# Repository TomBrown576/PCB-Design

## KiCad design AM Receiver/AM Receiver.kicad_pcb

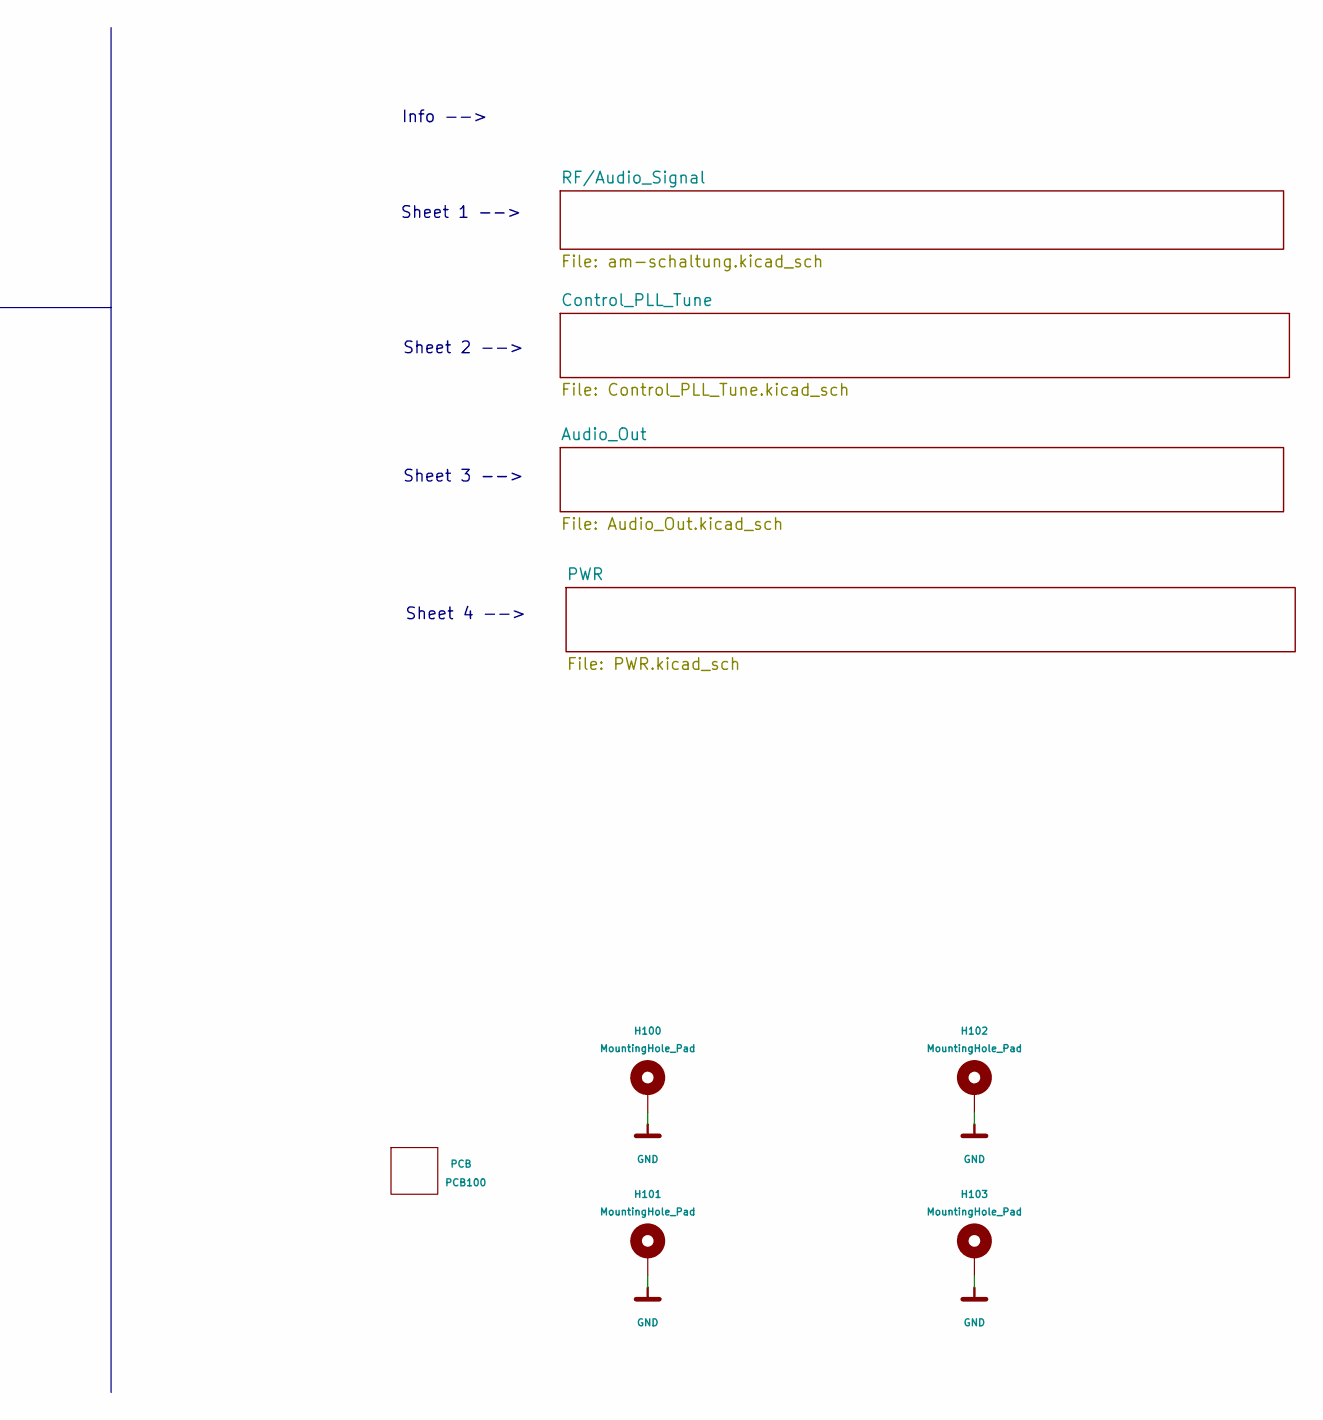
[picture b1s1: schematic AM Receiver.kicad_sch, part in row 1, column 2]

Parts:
H100, H101, H102, H103: MountingHole_Pad; MountingHole_3.2mm_M3_Pad
PCB100: PCB

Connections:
GND: H100.1 (1_1), H101.1 (1_1), H102.1 (1_1), H103.1 (1_1); also elsewhere on the board

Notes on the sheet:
Date 01.07.2026
Sheet 1 -->
Projekt Am Receiver with quadratur mixer
Info -->
Sheet 4 -->
Rev. 1.0
Sheet 3 -->
Name T.Brown
Sheet 2 -->
Changes, Modifications V1.0 Initial Revision Input Voltage 12V ... 15V
Gruppe Gruppe 12
Revision History

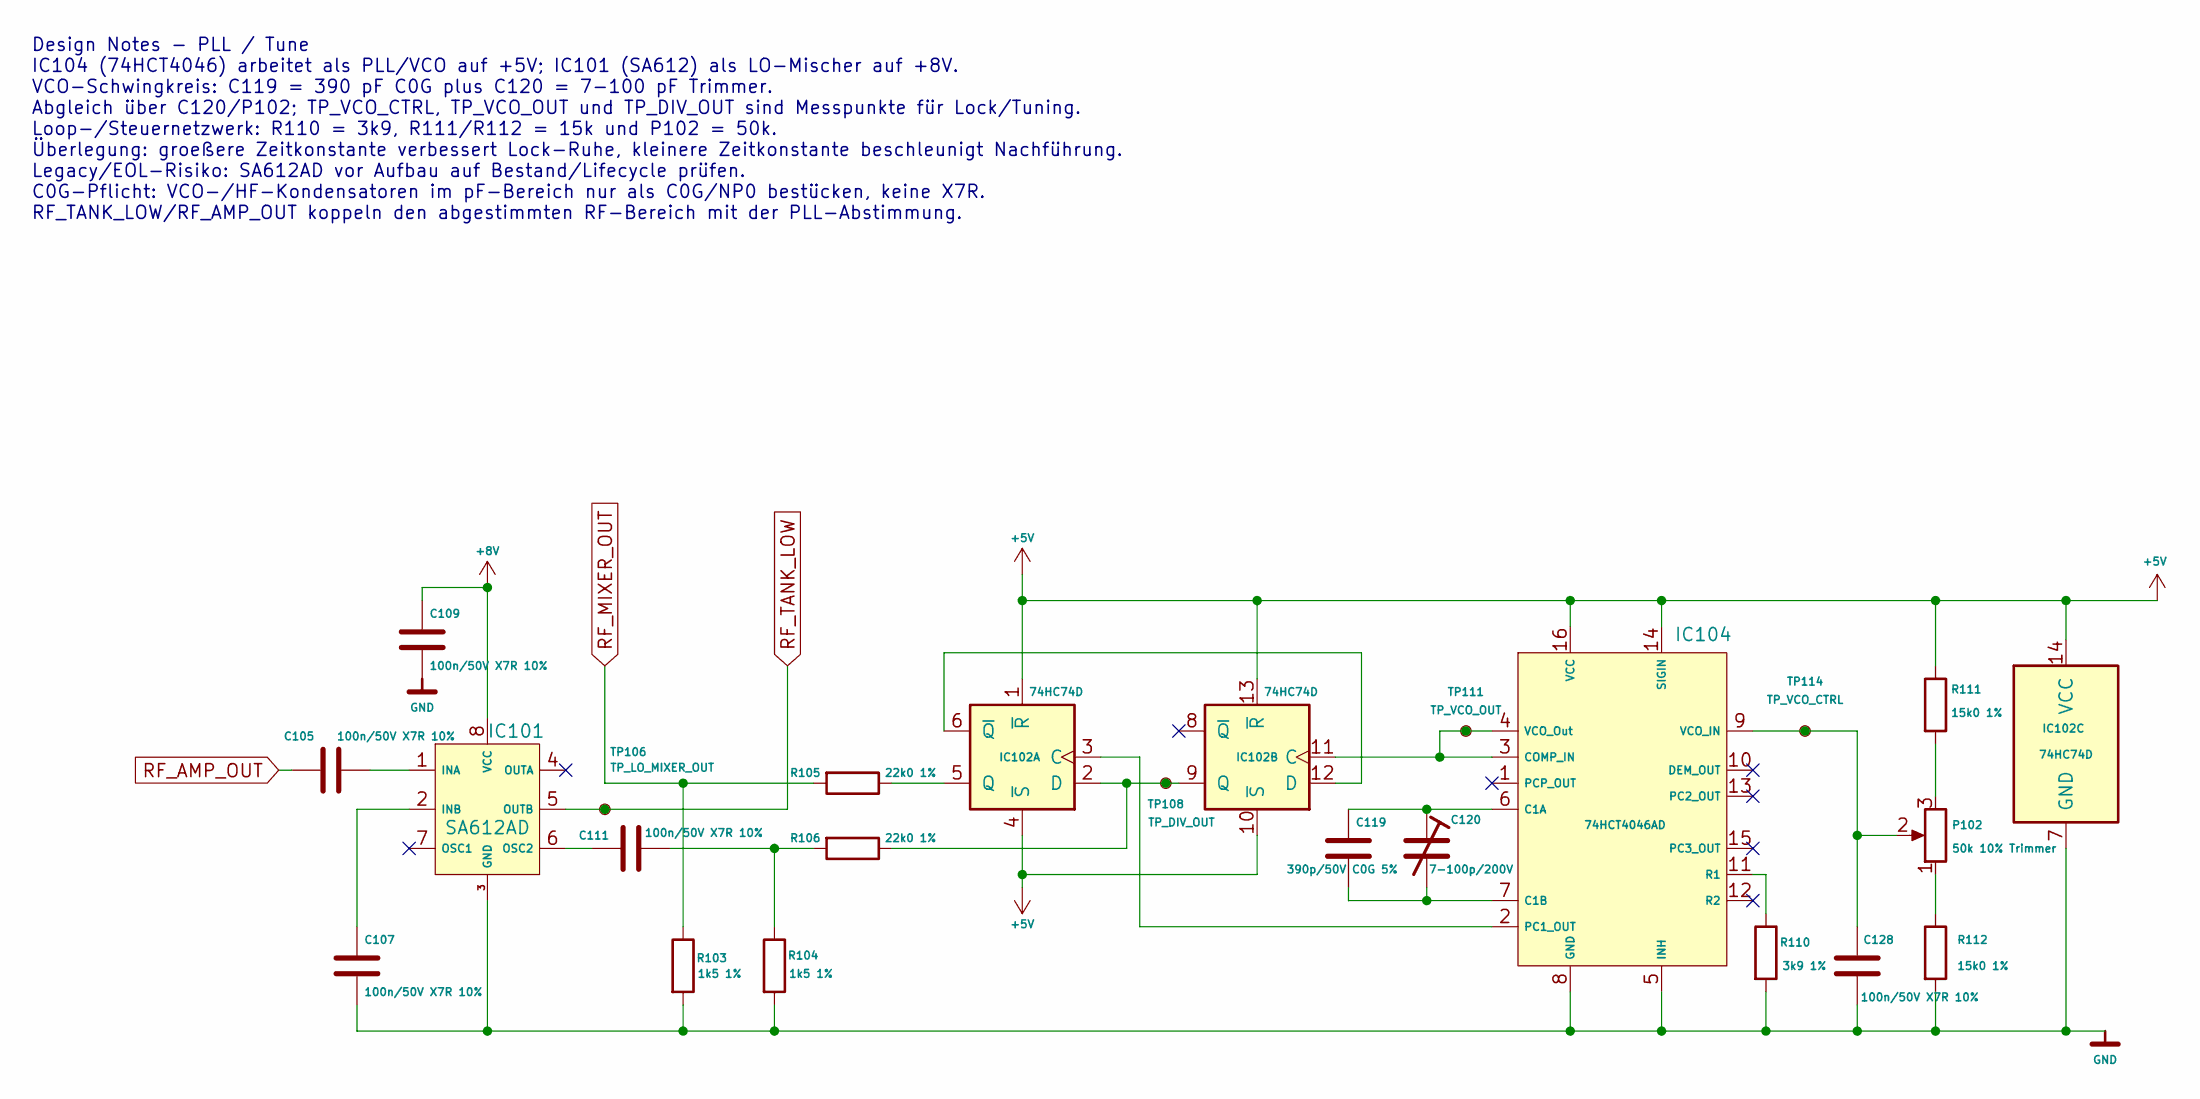
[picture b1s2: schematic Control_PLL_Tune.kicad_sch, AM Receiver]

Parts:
C105, C107, C109, C111, C128: 100n/50V X7R 10%; C_0603_1608Metric_Pad1.08x0.95mm_HandSolder
C119: 390p/50V C0G 5%; C_0603_1608Metric_Pad1.08x0.95mm_HandSolder
C120: 7-100p/200V; Vishay_BFC280907015_Trimmer_7-100pF
IC101: SA612AD; SOIC-8_3.9x4.9mm_P1.27mm
IC102: 74HC74D; SOIC-14_3.9x8.7mm_P1.27mm
IC104: 74HCT4046AD; SOIC-16_3.9x9.9mm_P1.27mm
P102: 50k 10% Trimmer; Potentiometer_Bourns_3386P_Vertical
R103, R104: 1k5 1%; R_0603_1608Metric_Pad0.98x0.95mm_HandSolder
R105, R106: 22k0 1%; R_0603_1608Metric_Pad0.98x0.95mm_HandSolder
R110: 3k9 1%; R_0603_1608Metric_Pad0.98x0.95mm_HandSolder
R111, R112: 15k0 1%; R_0603_1608Metric_Pad0.98x0.95mm_HandSolder
TP106: TP_LO_MIXER_OUT; TestPoint_Pad_D1.0mm
TP108: TP_DIV_OUT; TestPoint_Pad_D1.0mm
TP111: TP_VCO_OUT; TestPoint_Pad_D1.0mm
TP114: TP_VCO_CTRL; TestPoint_Pad_D1.0mm

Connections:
+5V: IC102.1 (~R), IC102.4 (~S), IC102.10 (~S), IC102.13 (~R), IC102.14 (VCC), IC104.14 (SIGIN), IC104.16 (VCC), R111.1; also elsewhere on the board
+8V: C109.1, IC101.8 (VCC); also elsewhere on the board
GND: C107.2, C109.2, C128.2, IC101.3 (GND), IC102.7 (GND), IC104.5 (INH), IC104.8 (GND), R103.2, R104.2, R110.2, R112.2; also elsewhere on the board
unnamed: C111.1, R104.1, R106.2
unnamed: C105.1, IC101.1 (INA)
unnamed: C107.1, IC101.2 (INB)
unnamed: C111.2, IC101.6 (OSC2)
unnamed: IC102.3 (C), IC104.2 (PC1_OUT)
unnamed: IC102.2 (D), IC102.9 (Q), R106.1, TP108.1 (1_1)
unnamed: IC102.5 (Q), R105.1
unnamed: IC102.6 (~Q), IC102.12 (D)
unnamed: IC102.11 (C), IC104.3 (COMP_IN), IC104.4 (VCO_Out), TP111.1 (1_1)
unnamed: C119.1, C120.1, IC104.6 (C1A)
unnamed: C119.2, C120.2, IC104.7 (C1B)
unnamed: IC104.11 (R1), R110.1
unnamed: C128.1, IC104.9 (VCO_IN), P102.2, TP114.1 (1_1)
unnamed: P102.1, R112.1
unnamed: P102.3, R111.2
RF_AMP_OUT: C105.2; also elsewhere on the board
RF_MIXER_OUT: R103.1, R105.2; also elsewhere on the board
RF_TANK_LOW: IC101.5 (OUTB), TP106.1 (1_1); also elsewhere on the board

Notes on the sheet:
Design Notes - PLL / Tune IC104 (74HCT4046) arbeitet als PLL/VCO auf +5V; IC101 (SA612) als LO-Mischer auf +8V. VCO-Schwingkreis: C119 = 390 pF C0G plus C120 = 7-100 pF Trimmer. Abgleich über C120/P102; TP_VCO_CTRL, TP_VCO_OUT und TP_DIV_OUT sind Messpunkte für Lock/Tuning. Loop-/Steuernetzwerk: R1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

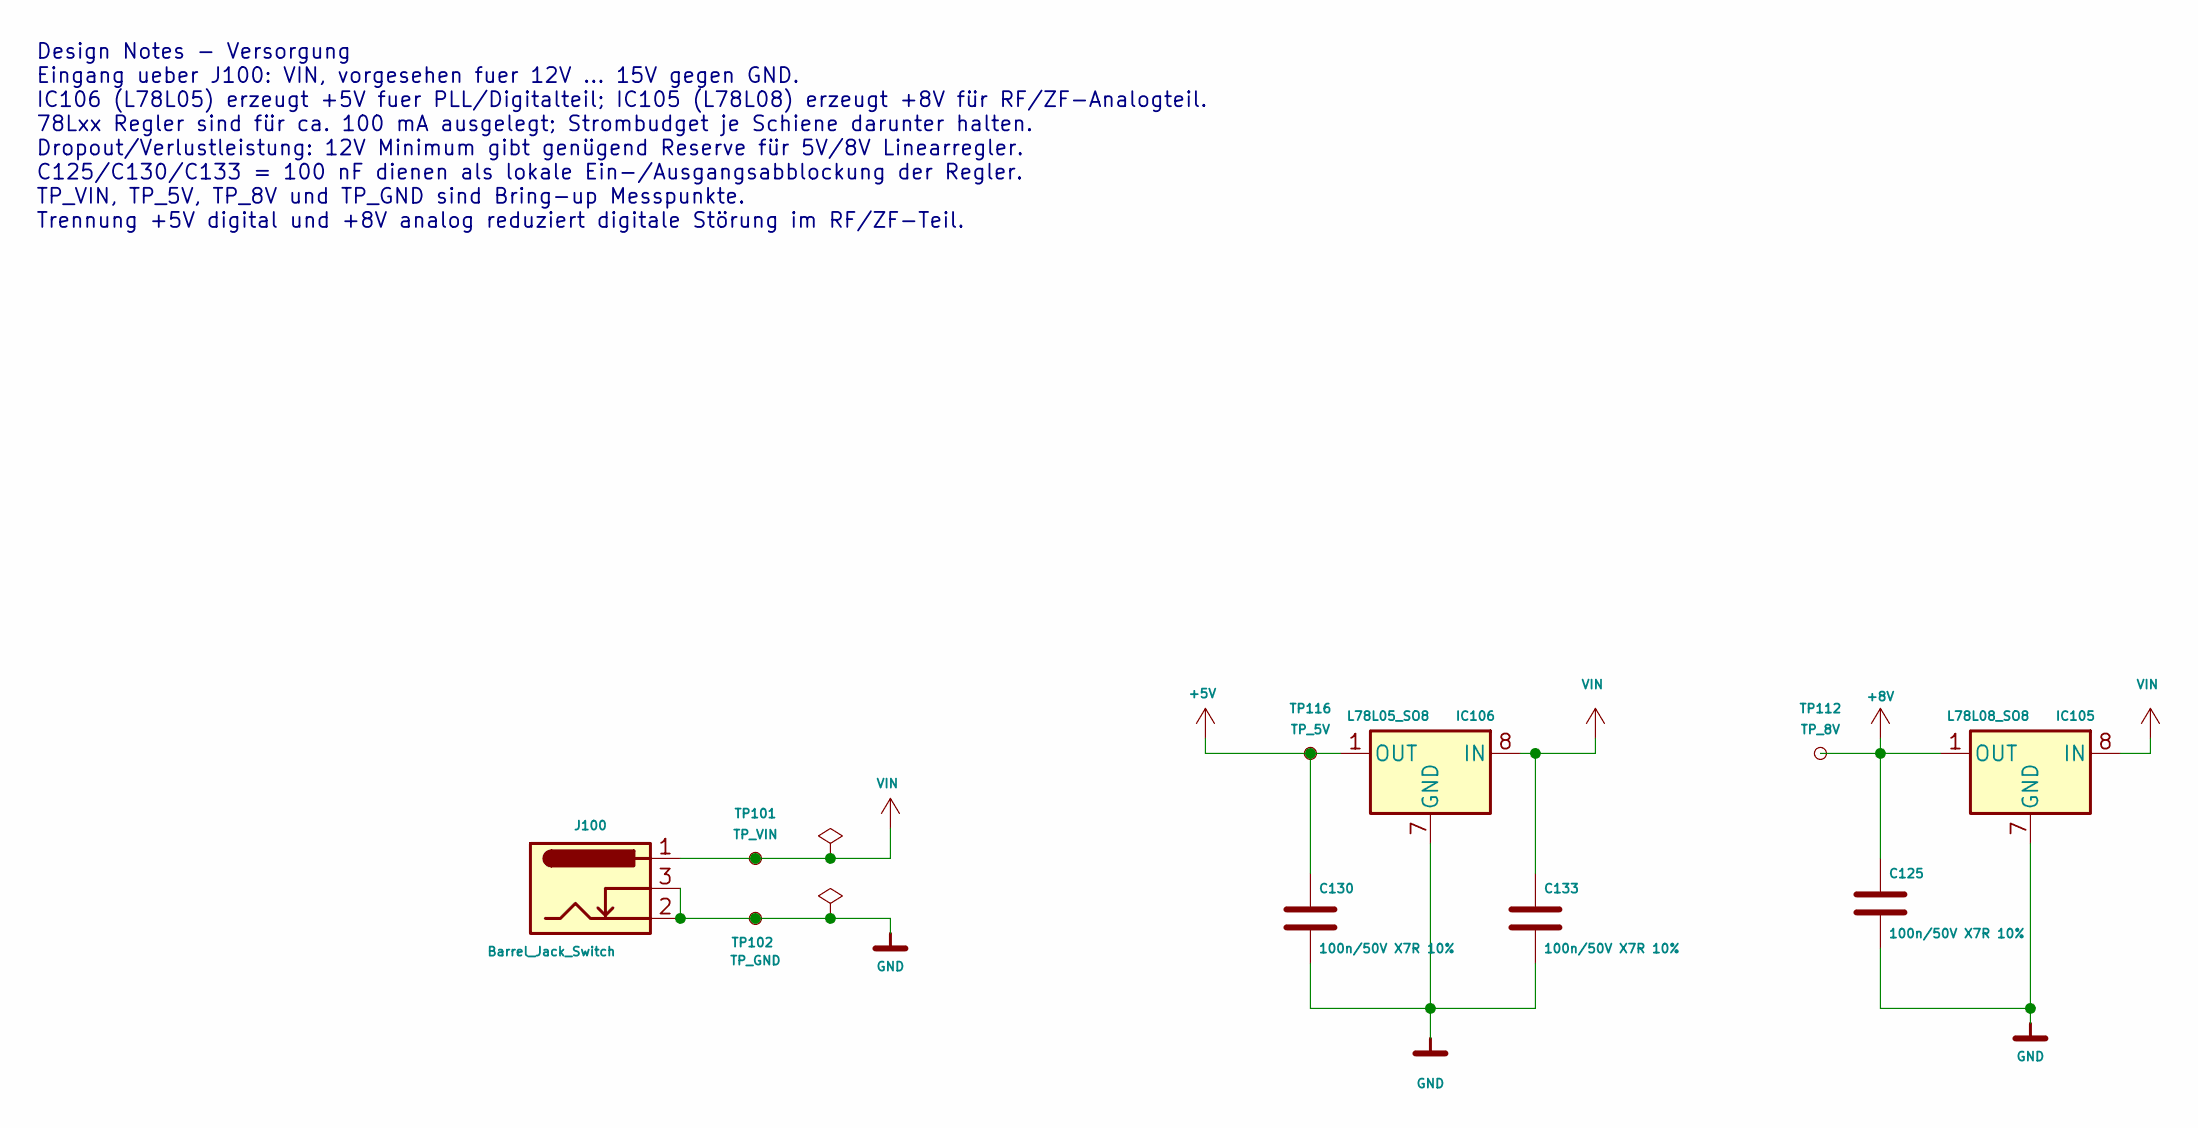
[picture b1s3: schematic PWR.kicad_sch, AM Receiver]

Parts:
C125, C130, C133: 100n/50V X7R 10%; C_0603_1608Metric_Pad1.08x0.95mm_HandSolder
IC105: L78L08_SO8; SOIC-8_3.9x4.9mm_P1.27mm
IC106: L78L05_SO8; SOIC-8_3.9x4.9mm_P1.27mm
J100: Barrel_Jack_Switch; BarrelJack_CUI_PJ-102AH_Horizontal
TP101: TP_VIN; TestPoint_Pad_D1.0mm
TP102: TP_GND; TestPoint_Pad_D1.0mm
TP112: TP_8V; TestPoint_Pad_D1.0mm
TP116: TP_5V; TestPoint_Pad_D1.0mm

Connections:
+5V: C130.1, IC106.1 (OUT), TP116.1 (1_1); also elsewhere on the board
+8V: C125.1, IC105.1 (OUT), TP112.1 (1_1); also elsewhere on the board
GND: C125.2, C130.2, C133.2, IC105.2 (GND), IC105.3 (GND), IC105.6 (GND), IC105.7 (GND), IC106.2 (GND), IC106.3 (GND), IC106.6 (GND), IC106.7 (GND), J100.2, J100.3, TP102.1 (1_1); also elsewhere on the board
VIN: C133.1, IC105.8 (IN), IC106.8 (IN), J100.1, TP101.1 (1_1); also elsewhere on the board

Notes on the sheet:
Design Notes - Versorgung Eingang ueber J100: VIN, vorgesehen fuer 12V ... 15V gegen GND. IC106 (L78L05) erzeugt +5V fuer PLL/Digitalteil; IC105 (L78L08) erzeugt +8V für RF/ZF-Analogteil. 78Lxx Regler sind für ca. 100 mA ausgelegt; Strombudget je Schiene darunter halten. Dropout/Verlustleistung: 12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

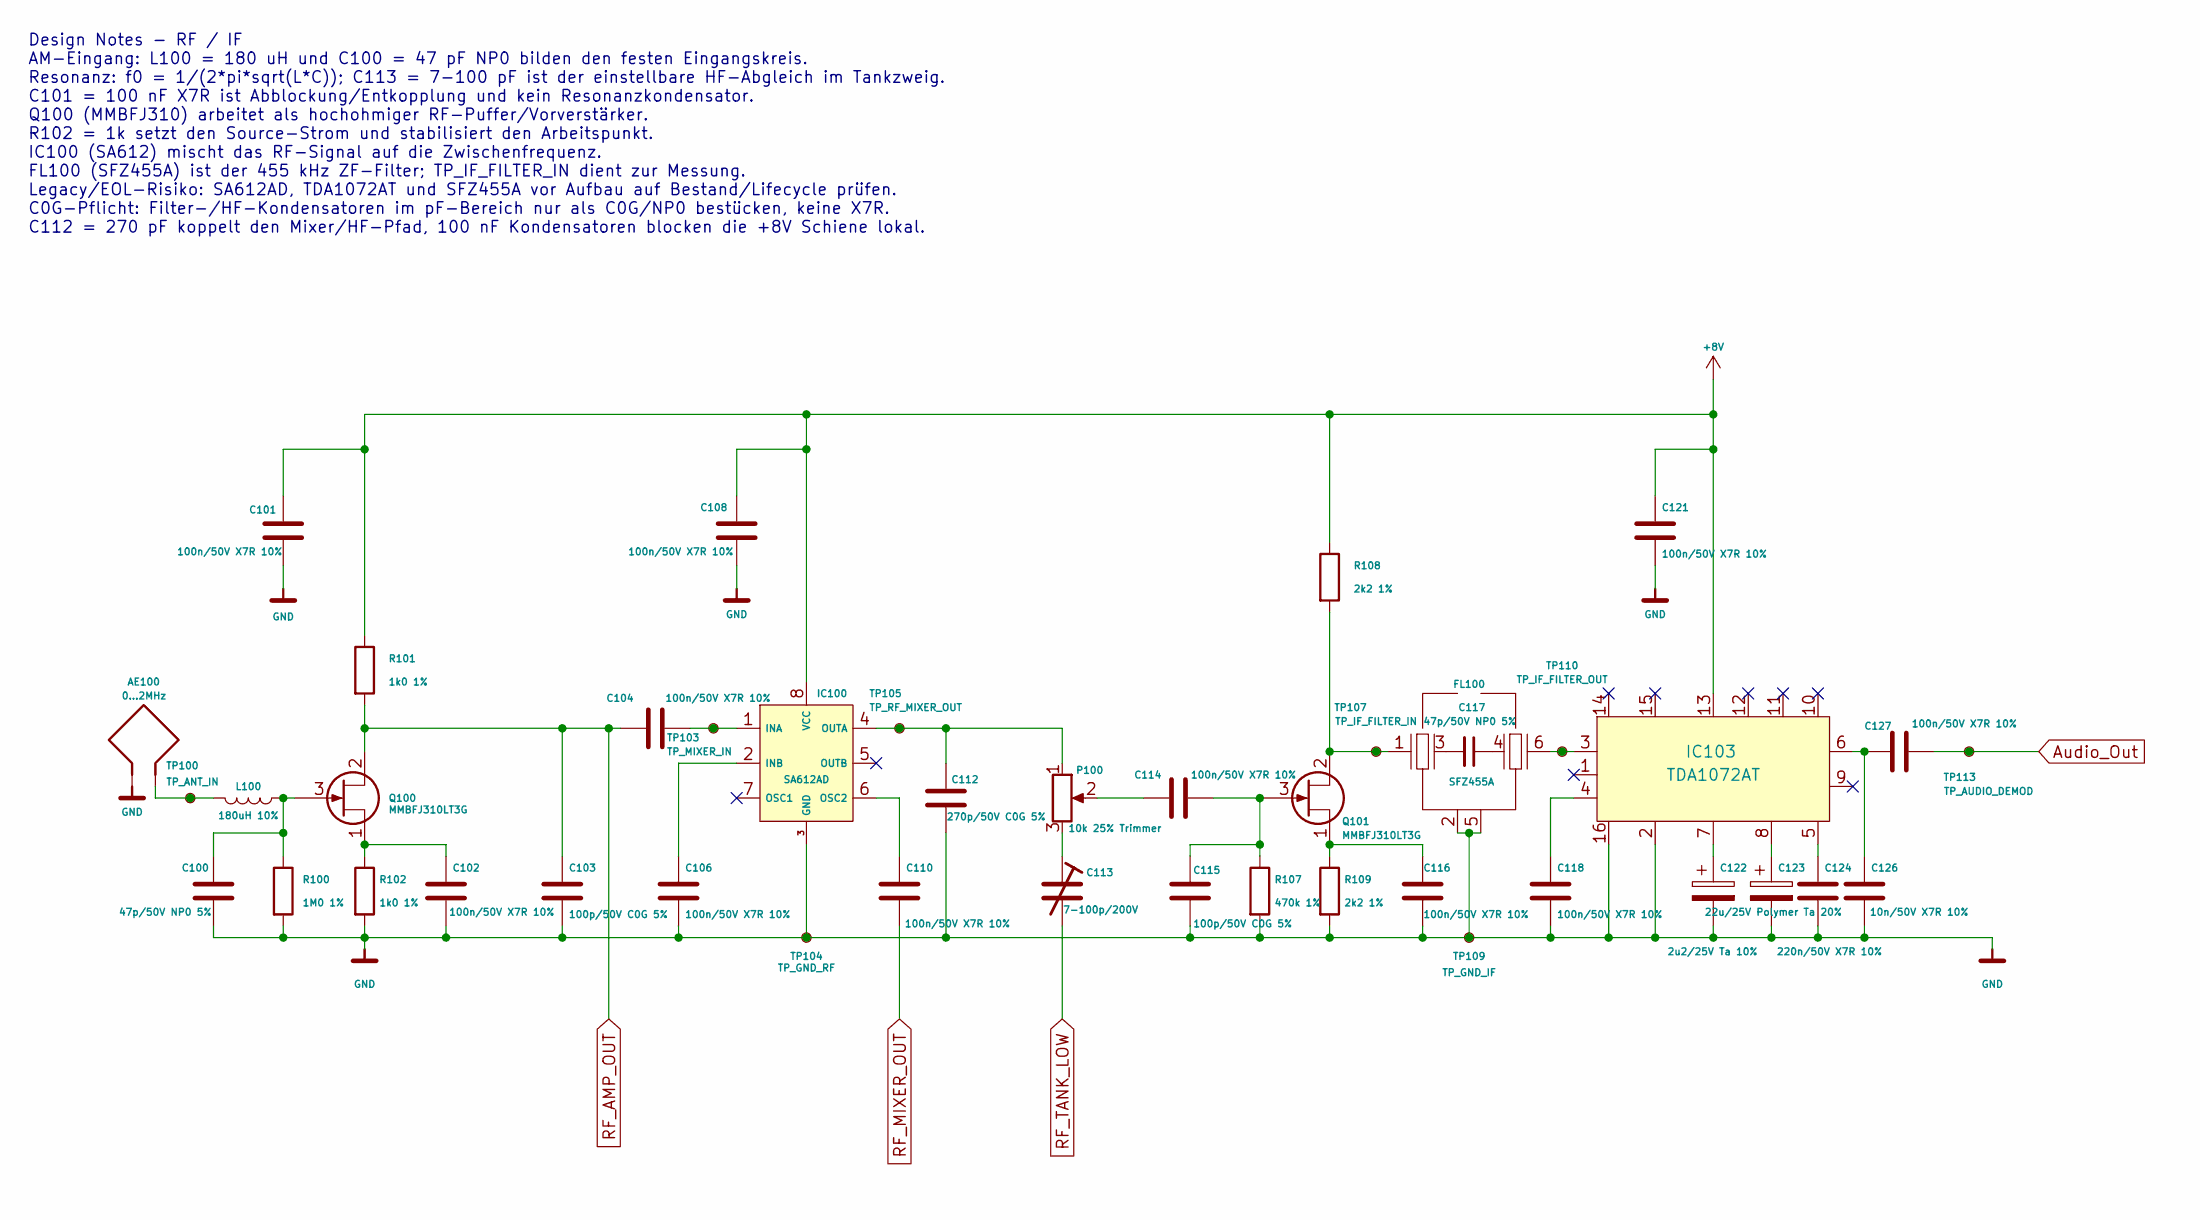
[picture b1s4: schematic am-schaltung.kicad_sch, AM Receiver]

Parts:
AE100: 0...2MHz; PinHeader_1x02_P2.54mm_Vertical
C100, C117: 47p/50V NP0 5%; C_0603_1608Metric_Pad1.08x0.95mm_HandSolder
C101, C102, C104, C106, C108, C110, C114, C116, C118, C121, C127: 100n/50V X7R 10%; C_0603_1608Metric_Pad1.08x0.95mm_HandSolder
C103, C115: 100p/50V C0G 5%; C_0603_1608Metric_Pad1.08x0.95mm_HandSolder
C112: 270p/50V C0G 5%; C_0603_1608Metric_Pad1.08x0.95mm_HandSolder
C113: 7-100p/200V; Vishay_BFC280907015_Trimmer_7-100pF
C122: 2u2/25V Ta 10%; CP_EIA-3216-18_Kemet-A_HandSolder
C123: 22u/25V Polymer Ta 20%; CP_EIA-3528-21_Kemet-B_HandSolder
C124: 220n/50V X7R 10%; C_0603_1608Metric_Pad1.08x0.95mm_HandSolder
C126: 10n/50V X7R 10%; C_0603_1608Metric_Pad1.08x0.95mm_HandSolder
FL100: SFZ455A
IC100: SA612AD; SOIC-8_3.9x4.9mm_P1.27mm
IC103: TDA1072AT; SOIC-16_3.9x9.9mm_P1.27mm
L100: 180uH 10%; L_1812_4532Metric_Pad1.30x3.40mm_HandSolder
P100: 10k 25% Trimmer; Potentiometer_Bourns_TC33X_Vertical
Q100, Q101: MMBFJ310LT3G; SOT-23_Handsoldering
R100: 1M0 1%; R_0603_1608Metric_Pad0.98x0.95mm_HandSolder
R101, R102: 1k0 1%; R_0603_1608Metric_Pad0.98x0.95mm_HandSolder
R107: 470k 1%; R_0603_1608Metric_Pad0.98x0.95mm_HandSolder
R108, R109: 2k2 1%; R_0603_1608Metric_Pad0.98x0.95mm_HandSolder
TP100: TP_ANT_IN; TestPoint_Pad_D1.0mm
TP103: TP_MIXER_IN; TestPoint_Pad_D1.0mm
TP104: TP_GND_RF; TestPoint_Pad_D1.0mm
TP105: TP_RF_MIXER_OUT; TestPoint_Pad_D1.0mm
TP107: TP_IF_FILTER_IN; TestPoint_Pad_D1.0mm
TP109: TP_GND_IF; TestPoint_Pad_D1.0mm
TP110: TP_IF_FILTER_OUT; TestPoint_Pad_D1.0mm
TP113: TP_AUDIO_DEMOD; TestPoint_Pad_D1.0mm

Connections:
+8V: C101.1, C108.1, C121.1, IC100.8 (VCC), IC103.13, R101.1, R108.1; also elsewhere on the board
Audio_Out: C127.1, TP113.1 (1_1); also elsewhere on the board
GND: AE100.1, C100.2, C101.2, C102.2, C103.2, C106.2, C108.2, C112.2, C115.2, C116.2, C118.2, C121.2, C122.2, C123.2, C124.2, C126.2, FL100.2, FL100.5, IC100.3 (GND), IC103.2, IC103.16, R100.2, R102.2, R107.2, R109.2, TP104.1 (1_1), TP109.1 (1_1); also elsewhere on the board
unnamed: AE100.2, L100.2, TP100.1 (1_1)
unnamed: C113.1, P100.3
unnamed: C114.2, P100.2
unnamed: C117.1, FL100.4
unnamed: C117.2, FL100.3
unnamed: C118.1, IC103.4
unnamed: C122.1, IC103.7
unnamed: C123.1, IC103.8
unnamed: C124.1, IC103.5
unnamed: C126.1, C127.2, IC103.6
unnamed: FL100.6, IC103.3, TP110.1 (1_1)
unnamed: C104.1, IC100.1 (INA), TP103.1 (1_1)
unnamed: C106.1, IC100.2 (INB)
unnamed: C110.1, IC100.6 (OSC2)
unnamed: C112.1, IC100.4 (OUTA), P100.1, TP105.1 (1_1)
unnamed: C100.1, L100.1, Q100.3 (G), R100.1
unnamed: C102.1, Q100.1 (S), R102.1
unnamed: FL100.1, Q101.2 (D), R108.2, TP107.1 (1_1)
unnamed: C114.1, C115.1, Q101.3 (G), R107.1
unnamed: C116.1, Q101.1 (S), R109.1
RF_AMP_OUT: C103.1, C104.2, Q100.2 (D), R101.2; also elsewhere on the board
RF_MIXER_OUT: C110.2; also elsewhere on the board
RF_TANK_LOW: C113.2; also elsewhere on the board

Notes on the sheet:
Design Notes - RF / IF AM-Eingang: L100 = 180 uH und C100 = 47 pF NP0 bilden den festen Eingangskreis. Resonanz: f0 = 1/(2*pi*sqrt(L*C)); C113 = 7-100 pF ist der einstellbare HF-Abgleich im Tankzweig. C101 = 100 nF X7R ist Abblockung/Entkopplung und kein Resonanzkondensator. Q100 (MMBFJ310) arbeite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

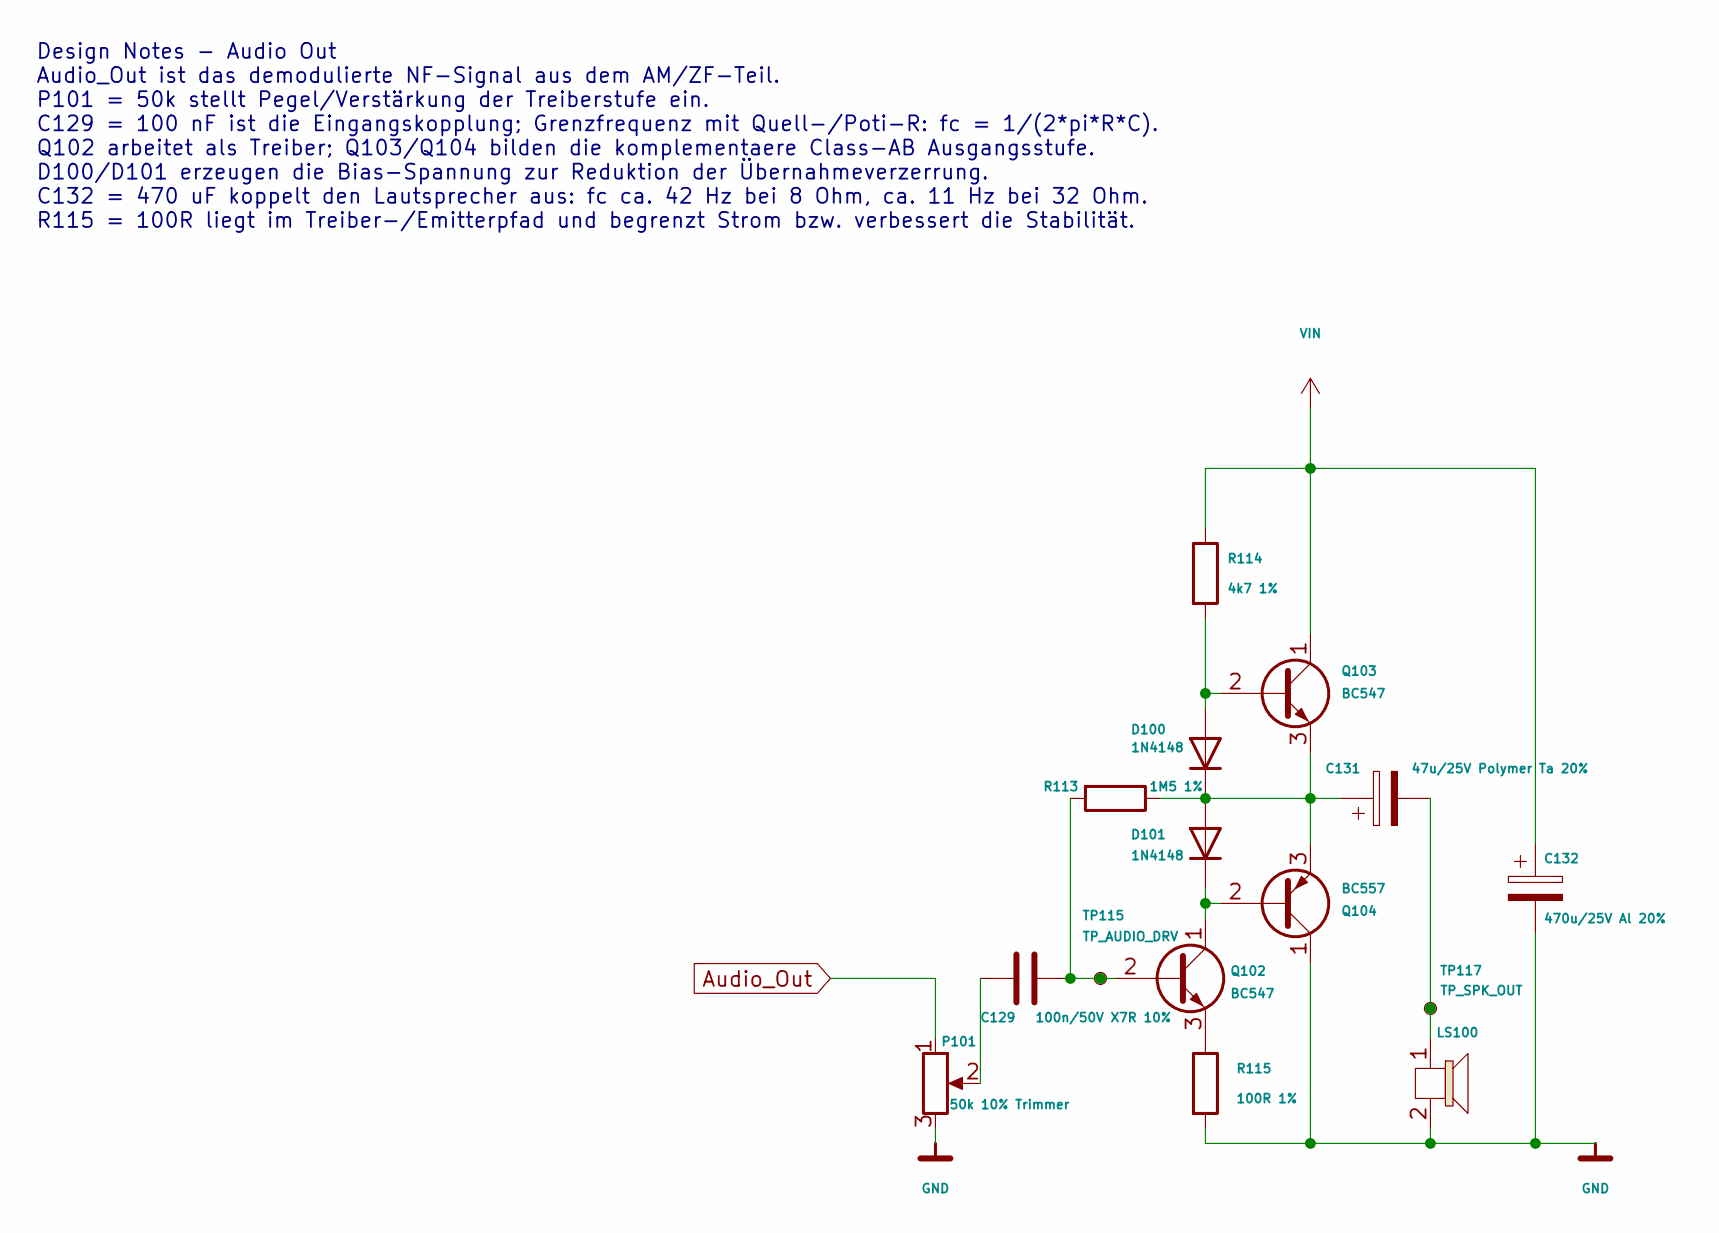
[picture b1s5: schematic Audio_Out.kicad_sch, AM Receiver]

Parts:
C129: 100n/50V X7R 10%; C_0603_1608Metric_Pad1.08x0.95mm_HandSolder
C131: 47u/25V Polymer Ta 20%; CP_EIA-7343-20_Kemet-V_HandSolder
C132: 470u/25V Al 20%; CP_Elec_10x10.5
D100, D101: 1N4148; D_SOD-123
LS100: TerminalBlock_Phoenix_MKDS-1,5-2-5.08_1x02_P5.08mm_Horizont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
P101: 50k 10% Trimmer; Potentiometer_Bourns_3386P_Vertical
Q102, Q103: BC547; TO-92_HandSolder
Q104: BC557; TO-92_HandSolder
R113: 1M5 1%; R_0603_1608Metric_Pad0.98x0.95mm_HandSolder
R114: 4k7 1%; R_0603_1608Metric_Pad0.98x0.95mm_HandSolder
R115: 100R 1%; R_0603_1608Metric_Pad0.98x0.95mm_HandSolder
TP115: TP_AUDIO_DRV; TestPoint_Pad_D1.0mm
TP117: TP_SPK_OUT; TestPoint_Pad_D1.0mm

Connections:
Audio_Out: P101.1; also elsewhere on the board
GND: C132.2, LS100.2, P101.3, Q104.1 (C), R115.2; also elsewhere on the board
unnamed: C129.2, P101.2
unnamed: C131.2, LS100.1, TP117.1 (1_1)
unnamed: D100.2 (A), Q103.2 (B), R114.2
unnamed: C131.1, D100.1 (K), D101.2 (A), Q103.3 (E), Q104.3 (E), R113.1
unnamed: D101.1 (K), Q102.1 (C), Q104.2 (B)
unnamed: C129.1, Q102.2 (B), R113.2, TP115.1 (1_1)
unnamed: Q102.3 (E), R115.1
VIN: C132.1, Q103.1 (C), R114.1; also elsewhere on the board

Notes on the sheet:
Design Notes - Audio Out Audio_Out ist das demodulierte NF-Signal aus dem AM/ZF-Teil. P101 = 50k stellt Pegel/Verstärkung der Treiberstufe ein. C129 = 100 nF ist die Eingangskopplung; Grenzfrequenz mit Quell-/Poti-R: fc = 1/(2*pi*R*C). Q102 arbeitet als Treiber; Q103/Q104 bilden die komplementaere 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

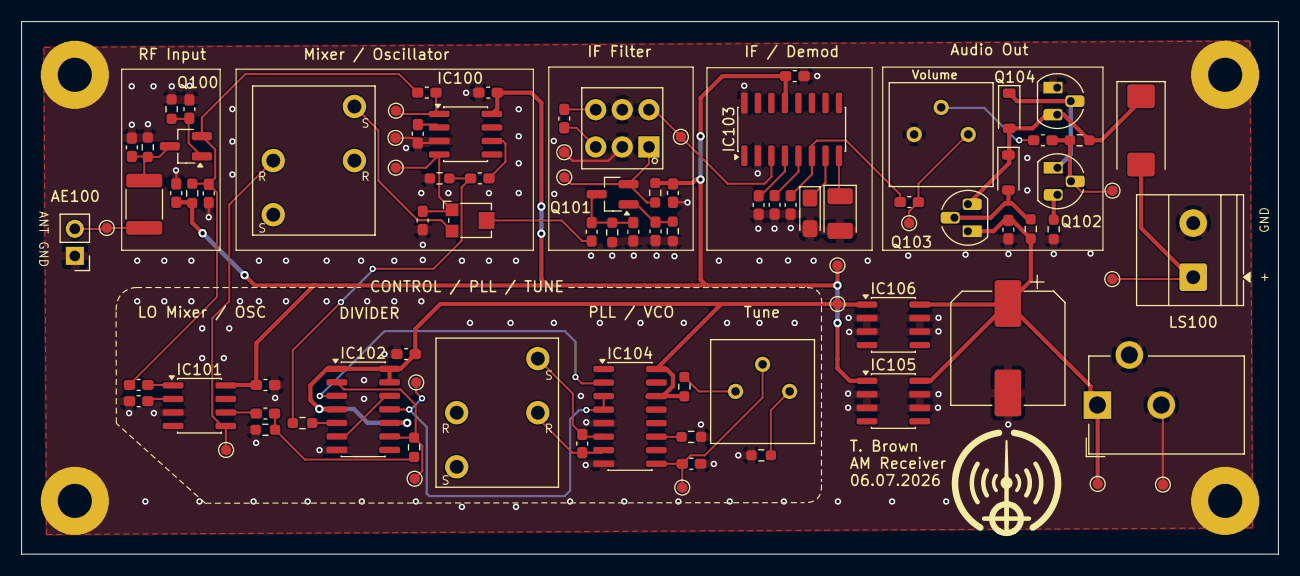
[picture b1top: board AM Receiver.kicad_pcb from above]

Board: 2 copper layers, 118.0 x 50.0 mm, 95 parts (0 on the bottom side), 50 nets.

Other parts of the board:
AM_Radio_Logo: AM_Radio_logo

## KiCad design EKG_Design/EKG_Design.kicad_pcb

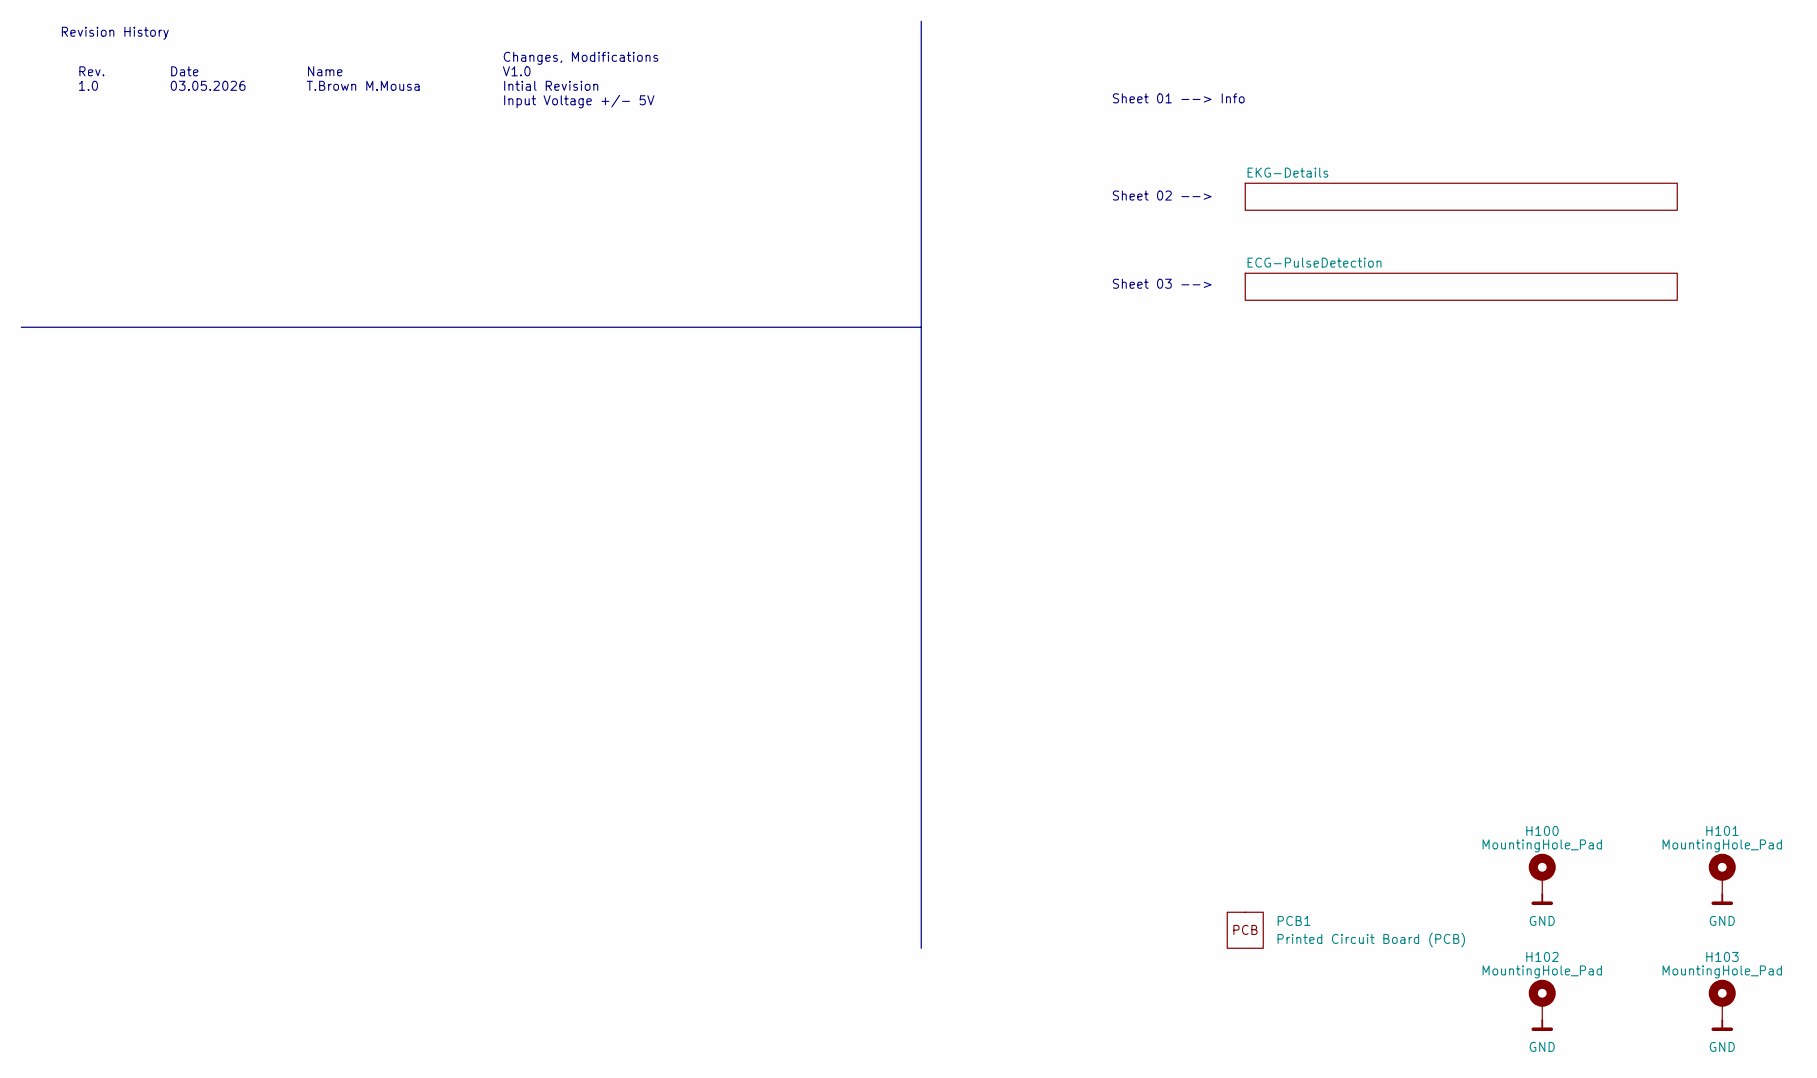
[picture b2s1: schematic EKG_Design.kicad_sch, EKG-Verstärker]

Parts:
H100, H101, H102, H103: MountingHole_Pad; MountingHole_2.2mm_M2_Pad
PCB1: Printed Circuit Board (PCB)

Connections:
GND: H100.1 (1_1), H101.1 (1_1), H102.1 (1_1), H103.1 (1_1); also elsewhere on the board

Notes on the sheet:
Rev. 1.0
Date 03.05.2026
Sheet 02 -->
Changes, Modifications V1.0 Intial Revision Input Voltage +/- 5V
Sheet 03 -->
Sheet 01 --> Info
Revision History
Name T.Brown M.Mousa
